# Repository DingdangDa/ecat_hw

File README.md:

# EtherCAT Hardware
Based on cleardrive

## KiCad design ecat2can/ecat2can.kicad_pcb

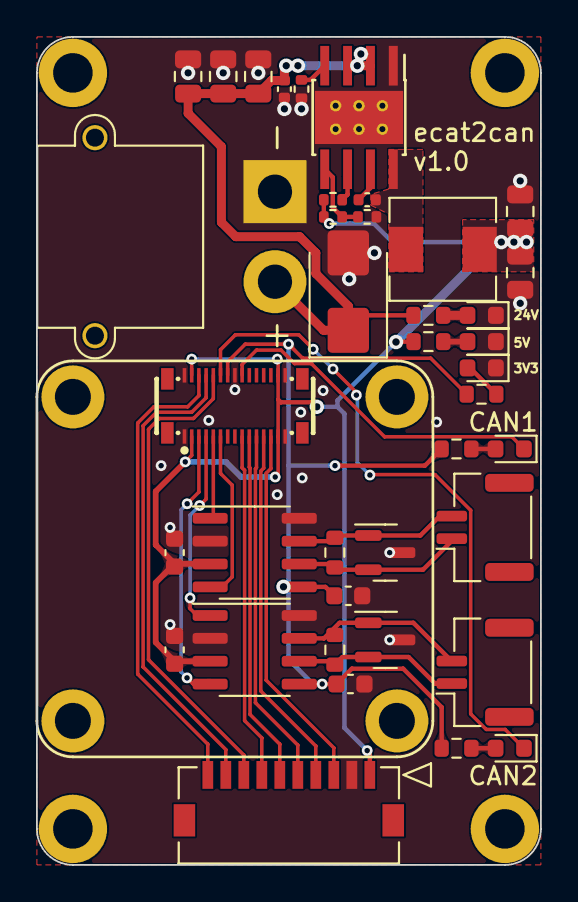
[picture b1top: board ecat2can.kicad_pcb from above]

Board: 2 copper layers, 28.0 x 46.0 mm, 47 parts (0 on the bottom side), 32 nets.

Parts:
C5, C6, C7, C8: 100n; C_0603_1608Metric
C9, C13: 100nF; C_0402_1005Metric
C10, C11, C12: 2.2uF/100V; C_0805_2012Metric
C14, C15: 47uF/10V; C_0805_2012Metric
D1, D2: BLUE; LED_0603_1608Metric
D3: GREEN; LED_0603_1608Metric
D4: YELLOW; LED_0603_1608Metric
D5: RED; LED_0603_1608Metric
D7: SMBJ58; D_SMB
H1, H2, H3, H10: Nut; SMD_NUT_M1.6
H4, H5, H6, H7: MountingHole; MountingHole_2.2mm_M2_DIN965_Pad
J1: 5013311007; CON_5013311007
J2, J3: Conn_01x02; JST_GH_SM02B-GHS-TB_1x02-1MP_P1.25mm_Horizontal
J5: Conn_01x02; AMASS_XT30PW-M_1x02_P2.50mm_Horizontal
J17: axt330224; CONN-SMD_30P-P0.40_AXT330224
L2: 15uH/2A; L_Chilisin_BMRB00050518-B
R4, R5, R8, R9: 1K; R_0603_1608Metric
R6, R7: 120; R_0603_1608Metric
R10: 20K; R_0603_1608Metric
R11: 64.9k; R_0402_1005Metric
R12: 100k; R_0402_1005Metric
R13: 40.2k; R_0402_1005Metric
R14: 10k; R_0402_1005Metric
U2, U3: TJA1051T-3; SOIC-8_3.9x4.9mm_P1.27mm
U4, U5: PESD1CAN; SOT-23
U6: LMR38020FDDAR; Texas_HTSOP-8-1EP_3.9x4.9mm_P1.27mm_EP2.95x4.9mm_Mask2.4x3.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

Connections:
3V3: C5.1, C6.1, J17.24, R4.2, R5.2, R8.2, U2.5 (VIO), U3.5 (VIO)
+5V: C7.1, C8.1, C14.1, C15.1, J1.1, J17.2, J17.14, J17.17, J17.29, L2.2, R9.2, R12.1, R13.1, U2.3 (VCC), U3.3 (VCC)
+48V: C9.1, C10.1, C11.1, C12.1, D7.1 (A1), J5.2, R10.2, U6.2 (EN), U6.3 (VIN)
/CAN1/CAN_H: J3.2, R7.1, U3.7 (CANH), U5.1 (H)
/CAN1/CAN_L: J3.1, R7.2, U3.6 (CANL), U5.2 (L)
/CAN/CAN_H: J2.2, R6.1, U2.7 (CANH), U4.1 (H)
/CAN/CAN_L: J2.1, R6.2, U2.6 (CANL), U4.2 (L)
/FDCAN1_RX: J17.6, U3.4 (RXD)
/FDCAN1_TX: J17.5, U3.1 (TXD)
/FDCAN2_RX: J17.3, U2.4 (RXD)
/FDCAN2_TX: J17.4, U2.1 (TXD)
/GPIO1: J1.10, J17.28
/GPIO2: J1.9, J17.27
/GPIO3: J1.8, J17.26
/GPIO4: J1.7, J17.9
/GPIO5: J1.6, J17.10
/GPIO6: J1.5, J17.11
/GPIO7: J1.4, J17.12
/GPIO8: J1.3, J17.13
/LED_CAN0: D1.1 (K), J17.22
/LED_CAN1: D2.1 (K), J17.25
GND: C5.2, C6.2, C7.2, C8.2, C9.2, C10.2, C11.2, C12.2, C14.2, C15.2, D3.1 (K), D4.1 (K), D5.1 (K), D7.2 (A2), J1.2, J5.1, J17.1, J17.15, J17.16, J17.23, J17.30, R11.2, R14.2, U2.2 (GND), U2.8 (S), U3.2 (GND), U3.8 (S), U4.3 (GND), U5.3 (GND), U6.1 (PGND), U6.9 (PAD)
unnamed: D1.2 (A), R4.1
unnamed: D2.2 (A), R5.1
unnamed: D3.2 (A), R8.1
unnamed: D4.2 (A), R9.1
unnamed: D5.2 (A), R10.1
unnamed: C13.2, U6.7 (BOOT)
unnamed: R13.2, R14.1, U6.5 (FB)
unnamed: R12.2, U6.6 (PG)
unnamed: R11.1, U6.4 (RT/SYNC)
unnamed: C13.1, L2.1, U6.8 (SW)

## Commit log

2024-04-23 Add usb2can v1.0
2024-04-23 Add ecat2can step
2024-04-28 Add origin to ecat2can
